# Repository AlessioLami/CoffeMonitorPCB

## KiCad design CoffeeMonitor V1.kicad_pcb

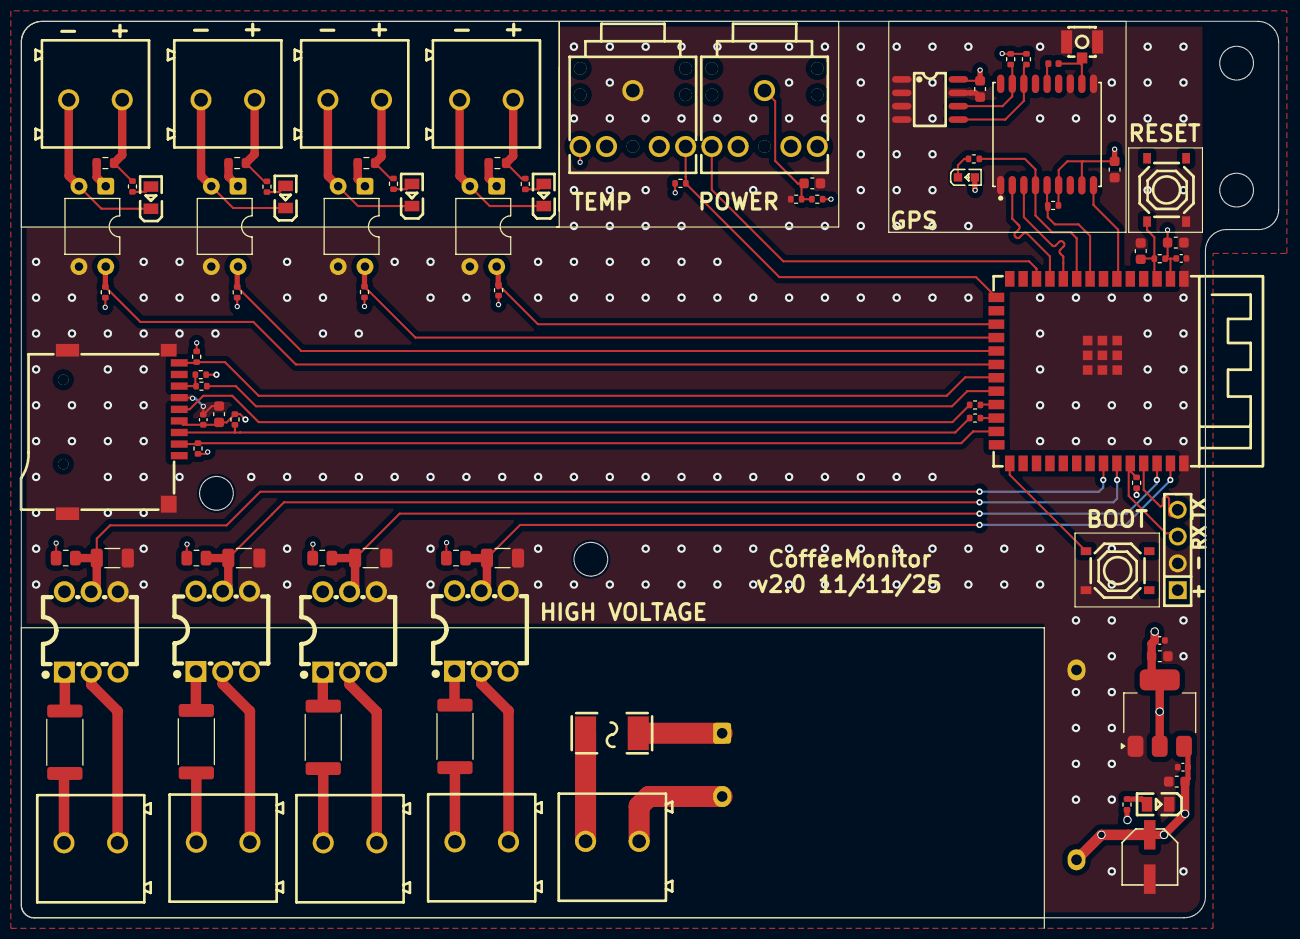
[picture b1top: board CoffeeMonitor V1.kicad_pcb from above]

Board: 4 copper layers, 119.2 x 85.0 mm, 95 parts (0 on the bottom side), 68 nets.

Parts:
C1, C2, C3, C4: 4.7uF; C_1206_3216Metric
C5, C6, C8, C9, C10, C13, C16, C18: 10uF; C_0603_1608Metric
C7: JVJ10V100M5X5; CAP-SMD_BD5.0-L5.3-W5.3-LS6.0-FD-H5.7
C11, C12, C14, C17: 100nF; C_0402_1005Metric
F1: MF2410F1.000TM; F2410
H1, H2, H3, H4: MountingHole; MountingHole_3.2mm_M3
H5: 2.54-1*4P母; HDR-TH_4P-P2.54-V-F
L1: 47nH; L_0402_1005Metric
LED1: ORH-B36G; LED0603-RD
LED2, LED3, LED4, LED5, LED6: 0805G (Green); LED0805-R-RD
P1, P2, P3, P4, P5, P6, P7, P8, P9: WJ500V-5.08-2P-14-00A; CONN-TH_2P-P5.00_WJ500V-5.08-2P
PJ1, PJ2: PJ-307_C2939173; AUDIO-TH_PJ-307
PS1: HLK-5M05; Converter_ACDC_Hi-Link_HLK-5Mxx
R1, R2, R3, R4: 68k; R_2512_6332Metric
R5, R6, R7, R8: 10k; R_0805_2012Metric
R9, R11, R13, R15: 2.2k; R_0603_1608Metric
R10, R12, R14, R16, R18, R19, R20, R21, R22, R23, R24, R25, R26, R27, R30, R32, R35, R36, R37: 10k; R_0402_1005Metric
R17: 680; R_0402_1005Metric
R28: 1k; R_0402_1005Metric
R29: 5.1k; R_0402_1005Metric
R31, R33, R34: 33; R_0402_1005Metric
SW1: ENABLE; SW-SMD_4P-L5.1-W5.1-P3.70-LS6.5-TL_H1.5
SW2: BOOT; SW-SMD_4P-L5.1-W5.1-P3.70-LS6.5-TL_H1.5
TF1: SH-TF-01A; TF-SMD_SH_SH-TF-01A
U1, U2, U3, U4: PC817; DIP-4_W7.62mm
U5, U6, U7, U8: H11AA1M; PDIP-6_L8.5-W6.5-P2.54-LS7.6-BL
U9: ESP32-S3-WROOM-1(N16R8); WIRELM-SMD_ESP32-S3-WROOM-1
U10: ATGM336H-5N31; GPSM-SMD_ATGM336H-TR
U11: AT24C32M/TR; SOP-8_L4.9-W3.9-P1.27-LS6.0-BL
U12: BWU.FL-IPEX1; IPEX-SMD_BWIPX-1-001E
U14: AMS1117-3.3; SOT-223-3_TabPin2

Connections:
+3.3V: C5.1, C6.1, C10.1, C12.1, C13.1, C14.1, C16.1, C17.1, H5.1, LED1.2 (A), PJ2.5, R5.2, R6.2, R7.2, R8.2, R10.2, R12.2, R14.2, R16.2, R22.1, R23.1, R25.1, R26.1, R27.1, R29.2, R30.2, R32.2, R35.2, R36.2, R37.2, TF1.4 (VDD), U9.2 (3V3), U10.6 (VBAT), U10.8 (VCC), U11.8 (VCC), U14.2 (VO)
+5V: C7.1, C9.1, C11.1, PS1.4 (+Vout), R28.1, U14.3 (VI)
/ADC1_CH7: PJ1.5, U9.12 (IO8)
/ADC1_CH8: PJ2.2, R25.2, U9.15 (IO3)
/BOOT: SW2.1 (A), U9.27 (IO0)
/CARD_DETECT: R32.1, TF1.9 (CD), U9.21 (IO13)
/CS: R30.1, TF1.2 (CD/DAT3), U9.25 (IO48)
/EN: C18.1, R29.1, SW1.1 (A), U9.3 (EN)
/GPS/SCL: R26.2, U10.17 (SCL), U11.6 (SCL)
/GPS/SDA: R27.2, U10.16 (SDA), U11.5 (SDA)
/IO1: C4.1, R8.1, U8.5 (C), U9.39 (IO1)
/IO2: C3.1, R7.1, U7.5 (C), U9.38 (IO2)
/IO6: U9.6 (IO6), U10.9 (NRESET)
/IO11: R16.1, U4.4, U9.17 (IO9)
/IO12: R14.1, U3.4, U9.18 (IO10)
/IO13: R12.1, U2.4, U9.19 (IO11)
/IO14: R10.1, U1.4, U9.20 (IO12)
/IO15: R22.2, U9.8 (IO15), U10.5 (ON/OFF)
/IO16: R17.2, U9.9 (IO16), U10.4 (1PPS)
/IO41: C1.1, R5.1, U5.5 (C), U9.34 (IO41)
/IO42: C2.1, R6.1, U6.5 (C), U9.35 (IO42)
/MISO: R34.2, U9.22 (IO14)
/MOSI: R31.2, U9.24 (IO47)
/SCK: R33.2, U9.23 (IO21)
/UART0_RX: H5.3, R35.1, U9.36 (RXD0)
/UART0_TX: H5.4, U9.37 (TXD0)
/UART1_RX: U9.11 (IO18), U10.2 (TXD)
/UART1_TX: U9.10 (IO17), U10.3 (RXD)
GND: C1.2, C2.2, C3.2, C4.2, C5.2, C6.2, C7.2, C8.2, C9.2, C10.2, C11.2, C12.2, C13.2, C14.2, C16.2, C17.2, C18.2, H5.2, LED6.2 (K), PJ2.1, PS1.3 (-Vout), R24.2, SW1.3 (C), SW2.3 (C), TF1.6 (VSS), TF1.10 (GND), TF1.11 (GND), TF1.12 (GND), TF1.13 (GND), U1.3, U2.3, U3.3, U4.3, U5.4 (E), U6.4 (E), U7.4 (E), U8.4 (E), U9.1 (GND), U9.40 (GND), U9.41 (GND), U10.1 (GND), U10.10 (GND), U10.12 (GND), U11.1 (A0), U11.2 (A1), U11.3 (A2), U11.4 (GND), U11.7 (WP), U12.2, U12.3, U14.1 (GND)
unnamed: C8.1, PJ1.1, R23.2, R24.1
unnamed: F1.1, P9.2
unnamed: LED1.1 (C), R17.1
unnamed: LED2.1 (A), R18.1
unnamed: LED2.2 (K), P5.1, U1.2
unnamed: LED3.1 (A), R19.1
unnamed: LED3.2 (K), P6.1, U2.2
unnamed: LED4.1 (A), R20.1
unnamed: LED4.2 (K), P7.1, U3.2
unnamed: LED5.1 (A), R21.1
unnamed: LED5.2 (K), P8.1, U4.2
unnamed: LED6.1 (A), R28.2
unnamed: P1.1, U5.2
unnamed: P1.2, R1.1
unnamed: P2.1, U6.2
unnamed: P2.2, R2.1
unnamed: P3.1, U7.2
unnamed: P3.2, R3.1
unnamed: P4.1, U8.2
unnamed: P4.2, R4.1
unnamed: P5.2, R9.1, R18.2
unnamed: P6.2, R11.1, R19.2
unnamed: P7.2, R13.1, R20.2
unnamed: P8.2, R15.1, R21.2
unnamed: F1.2, PS1.1 (AC/L)
unnamed: P9.1, PS1.2 (AC/N)
unnamed: R1.2, U5.1
unnamed: R2.2, U6.1
unnamed: R3.2, U7.1
unnamed: R4.2, U8.1
unnamed: R9.2, U1.1
unnamed: R11.2, U2.1
unnamed: R13.2, U3.1
unnamed: R15.2, U4.1
unnamed: R33.1, TF1.5 (CLK)
unnamed: R31.1, R37.1, TF1.3 (CMD)
unnamed: R34.1, R36.1, TF1.7 (DAT0)
unnamed: L1.2, U10.11 (RF_IN), U12.1
unnamed: L1.1, U10.14 (VCC_RF)

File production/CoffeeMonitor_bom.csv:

Designator,Footprint,Quantity,Value,LCSC Part #
"C1, C2, C3, C4",1206,4,4.7uF,
"C10, C13, C16, C5, C6, C8, C9",0603,7,10uF,
"C11, C12, C14, C15, C17",0402,5,100nF,
C7,CAP-SMD_BD5.0-L5.3-W5.3-LS6.0-FD-H5.7,1,JVJ10V100M5X5,C46550392
F1,F2410,1,MF2410F1.000TM,C83798
H5,HDR-TH_4P-P2.54-V-F,1,2.54-1*4P母,C2718488
L1,0402,1,47nH,
LED1,LED0603-RD,1,ORH-B36G,C193191
"LED2, LED3, LED4, LED5, LED6",LED0805-R-RD,5,0805G (Green),C2297
"P1, P2, P3, P4, P5, P6, P7, P8, P9",CONN-TH_2P-P5.00_WJ500V-5.08-2P,9,WJ500V-5.08-2P-14-00A,C8465
"PJ1, PJ2",AUDIO-TH_PJ-307,2,PJ-307_C2939173,C2939173
PS1,Converter_ACDC_Hi-Link_HLK-5Mxx,1,HLK-5M05,
"R1, R2, R3, R4",2512,4,68k,
"R10, R12, R14, R16, R18, R19, R20, R21, R22, R23, R24, R25, R26, R27, R29, R30, R32",0402,17,10k,
"R11, R13, R15, R9",0603,4,2.2k,
R17,0402,1,680,
R28,0402,1,1k,
"R31, R33, R34",0402,3,33,
"R5, R6, R7, R8",0805,4,10k,
SW1,SW-SMD_4P-L5.1-W5.1-P3.70-LS6.5-TL_H1.5,1,ENABLE,C318884
SW2,SW-SMD_4P-L5.1-W5.1-P3.70-LS6.5-TL_H1.5,1,BOOT,C318884
TF1,TF-SMD_SH_SH-TF-01A,1,SH-TF-01A,C22383473
"U1, U2, U3, U4",DIP-4_W7.62mm,4,PC817,
U10,GPSM-SMD_ATGM336H-TR,1,ATGM336H-5N31,C90770
U11,SOP-8_L4.9-W3.9-P1.27-LS6.0-BL,1,AT24C32M/TR,C2688466
U12,IPEX-SMD_BWIPX-1-001E,1,BWU.FL-IPEX1,C5137195
U14,SOT-223-3_TabPin2,1,AMS1117-3.3,
"U5, U6, U7, U8",PDIP-6_L8.5-W6.5-P2.54-LS7.6-BL,4,H11AA1M,C416004
U9,WIRELM-SMD_ESP32-S3-WROOM-1,1,ESP32-S3-WROOM-1(N16R8),C2913202

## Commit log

2025-11-04 Project init
2025-11-11 Finished CoffeeMonitor PCB
2025-11-11 Added STEP file
